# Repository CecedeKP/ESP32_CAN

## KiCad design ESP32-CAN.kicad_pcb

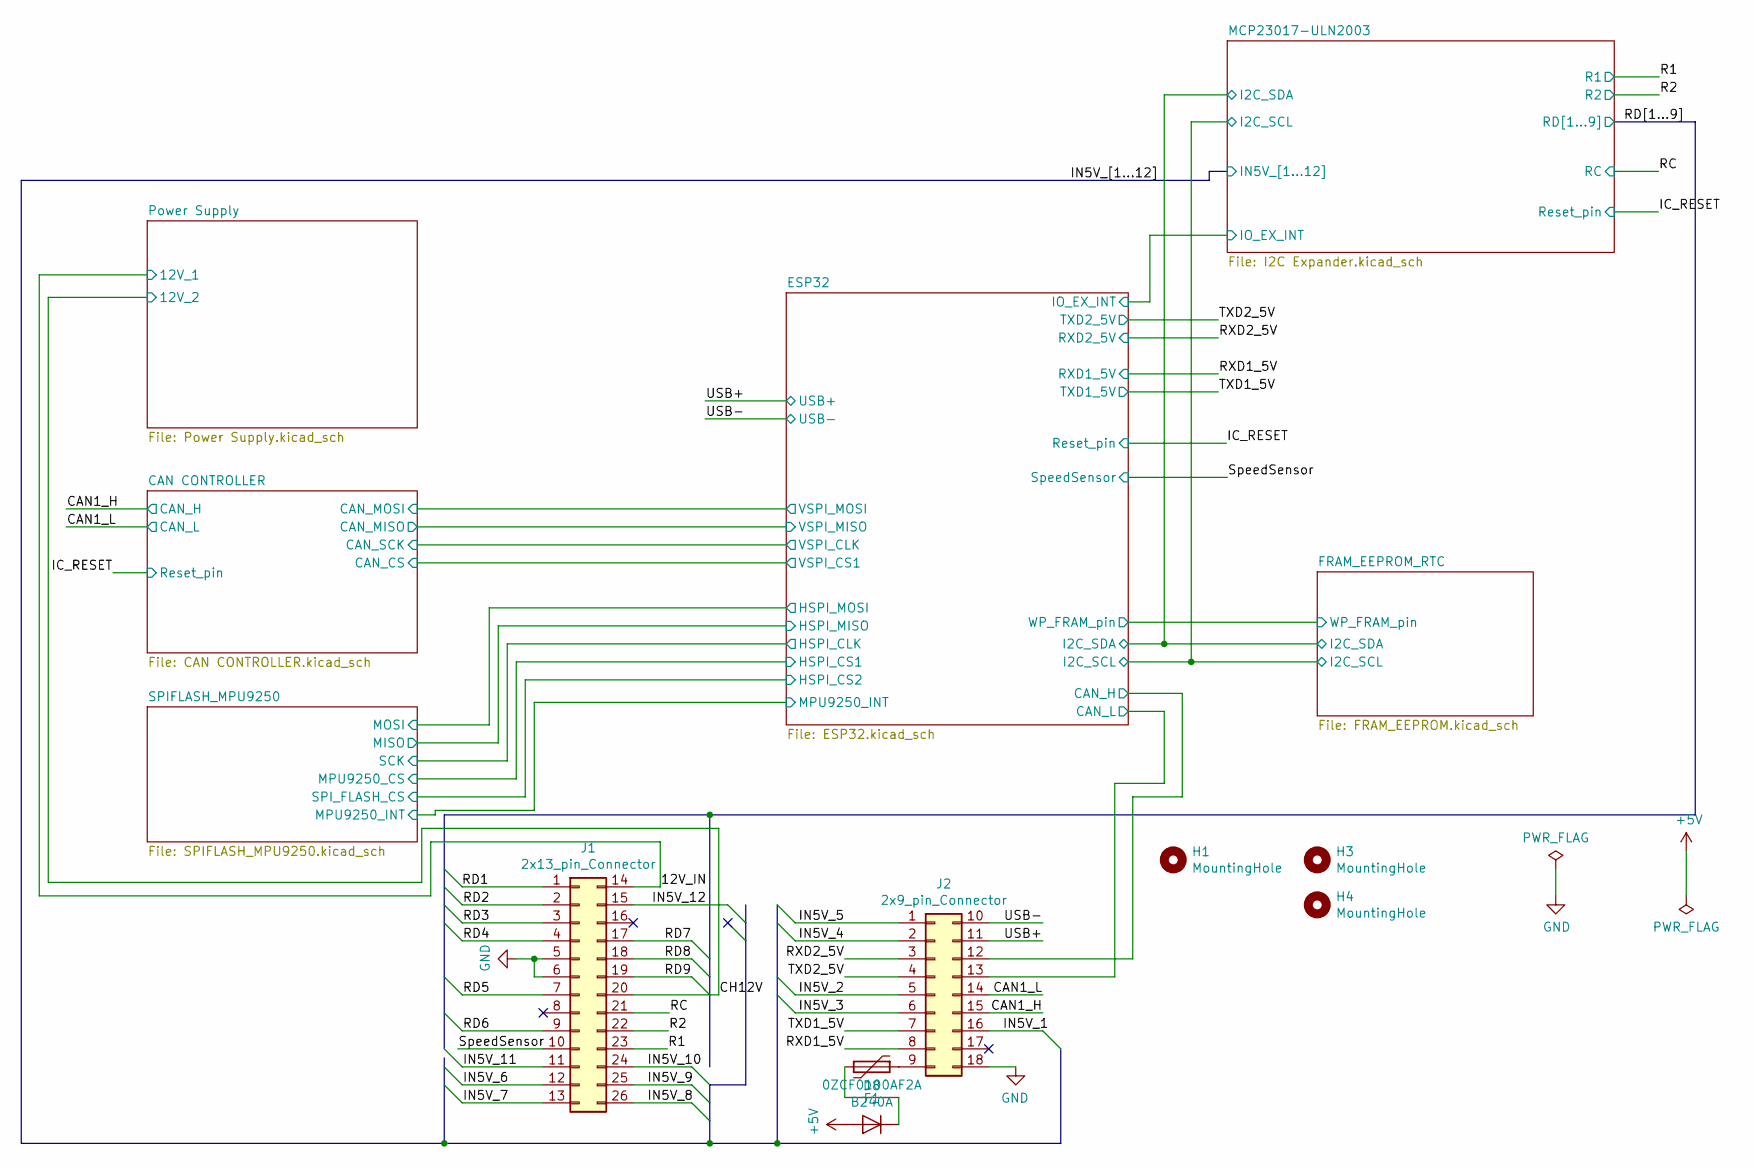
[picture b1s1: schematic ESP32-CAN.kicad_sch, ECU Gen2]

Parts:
D8: B240A; D_SMA
F1: 0ZCF0100AF2A; Fuse_2920_7451Metric
H1, H3, H4: MountingHole; MountingHole_3.2mm_M3_Pad_Via
J1: 2x13_pin_Connector; 3126A0312
J2: 2x9_pin_Connector; 3118A0312

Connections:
+5V: D8.2 (A); also elsewhere on the board
/12V_IN: J1.14; also elsewhere on the board
/CAN1_H: J2.15; also elsewhere on the board
/CAN1_L: J2.14; also elsewhere on the board
/CH12V: J1.20; also elsewhere on the board
/ESP32/CAN_H: J2.12; also elsewhere on the board
/ESP32/CAN_L: J2.13; also elsewhere on the board
/IN5V_1: J2.16; also elsewhere on the board
/IN5V_2: J2.5; also elsewhere on the board
/IN5V_3: J2.6; also elsewhere on the board
/IN5V_4: J2.2; also elsewhere on the board
/IN5V_5: J2.1; also elsewhere on the board
/IN5V_6: J1.12; also elsewhere on the board
/IN5V_7: J1.13; also elsewhere on the board
/IN5V_8: J1.26; also elsewhere on the board
/IN5V_9: J1.25; also elsewhere on the board
/IN5V_10: J1.24; also elsewhere on the board
/IN5V_11: J1.11; also elsewhere on the board
/IN5V_12: J1.15; also elsewhere on the board
/R1: J1.23; also elsewhere on the board
/R2: J1.22; also elsewhere on the board
/RC: J1.21; also elsewhere on the board
/RD1: J1.1; also elsewhere on the board
/RD2: J1.2; also elsewhere on the board
/RD3: J1.3; also elsewhere on the board
/RD4: J1.4; also elsewhere on the board
/RD5: J1.7; also elsewhere on the board
/RD6: J1.9; also elsewhere on the board
/RD7: J1.17; also elsewhere on the board
/RD8: J1.18; also elsewhere on the board
/RD9: J1.19; also elsewhere on the board
/RXD1_5V: J2.8; also elsewhere on the board
/RXD2_5V: J2.3; also elsewhere on the board
/SpeedSensor: J1.10; also elsewhere on the board
/TXD1_5V: J2.7; also elsewhere on the board
/TXD2_5V: J2.4; also elsewhere on the board
/USB+: J2.11; also elsewhere on the board
/USB-: J2.10; also elsewhere on the board
GND: J1.5, J1.6, J2.18; also elsewhere on the board
unnamed: D8.1 (K), F1.2
unnamed: F1.1, J2.9

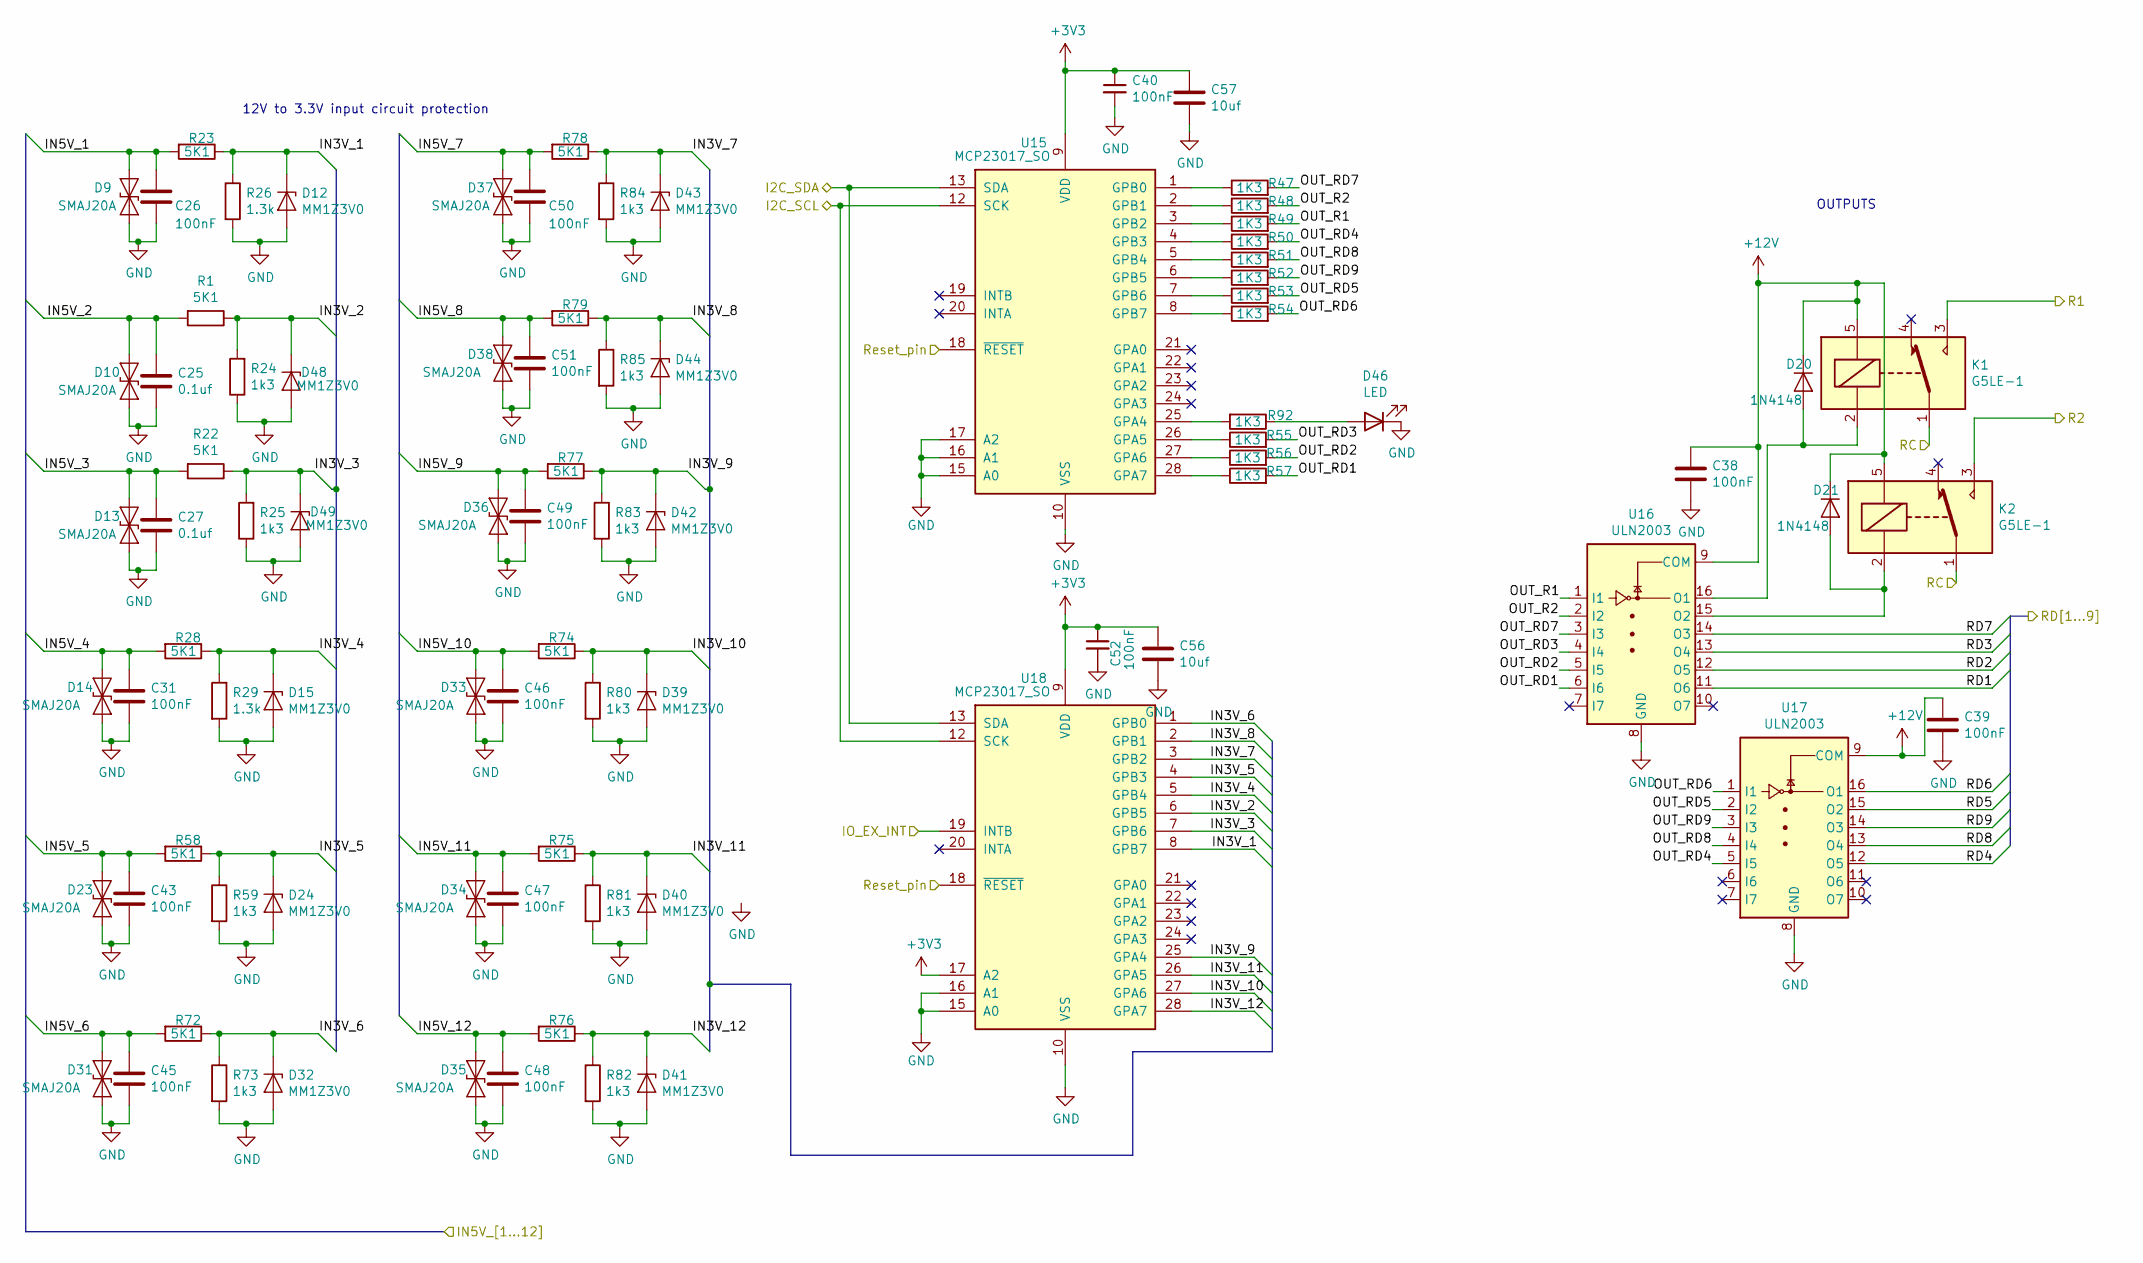
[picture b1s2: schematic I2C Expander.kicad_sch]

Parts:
C25, C27: 0.1uf; C_0603_1608Metric
C26, C31, C38, C39, C40, C43, C45, C46, C47, C48, C49, C50, C51, C52: 100nF; C_0603_1608Metric
C56, C57: 10uf; C_0603_1608Metric
D9, D10, D13, D14, D23, D31, D33, D34, D35, D36, D37, D38: SMAJ20A; D_SMA
D12, D15, D24, D32, D39, D40, D41, D42, D43, D44, D48, D49: MM1Z3V0; D_SOD-123
D20, D21: 1N4148; D_MiniMELF
D46: LED; LED_0603_1608Metric
K1, K2: G5LE-1; Relay_SPDT_Omron-G5LE-1
R1, R22, R23, R28, R58, R72, R74, R75, R76, R77, R78, R79: 5K1; R_0603_1608Metric
R24, R25, R59, R73, R80, R81, R82, R83, R84, R85: 1k3; R_0603_1608Metric
R26, R29: 1.3k; R_0603_1608Metric
R47, R48, R49, R50, R51, R52, R53, R54, R55, R56, R57, R92: 1K3; R_0603_1608Metric
U15, U18: MCP23017_SO; SOIC-28W_7.5x17.9mm_P1.27mm
U16, U17: ULN2003; SOIC-16_3.9x9.9mm_P1.27mm

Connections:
+12V: C38.1, C39.1, D20.1 (K), D21.1 (K), K1.5, K2.5, U16.9 (COM), U17.9 (COM); also elsewhere on the board
/ESP32/I2C_SCL: U15.12 (SCK), U18.12 (SCK); also elsewhere on the board
/ESP32/I2C_SDA: U15.13 (SDA), U18.13 (SDA); also elsewhere on the board
/ESP32/IO_EX_INT: U18.19 (INTB); also elsewhere on the board
/IC_RESET: U15.18 (~RESET), U18.18 (~RESET); also elsewhere on the board
/IN5V_1: C26.1, D9.1 (A1), R23.2; also elsewhere on the board
/IN5V_2: C25.1, D10.1 (A1), R1.2; also elsewhere on the board
/IN5V_3: C27.1, D13.1 (A1), R22.2; also elsewhere on the board
/IN5V_4: C31.1, D14.1 (A1), R28.2; also elsewhere on the board
/IN5V_5: C43.1, D23.1 (A1), R58.2; also elsewhere on the board
/IN5V_6: C45.1, D31.1 (A1), R72.2; also elsewhere on the board
/IN5V_7: C50.1, D37.1 (A1), R78.2; also elsewhere on the board
/IN5V_8: C51.1, D38.1 (A1), R79.2; also elsewhere on the board
/IN5V_9: C49.1, D36.1 (A1), R77.2; also elsewhere on the board
/IN5V_10: C46.1, D33.1 (A1), R74.2; also elsewhere on the board
/IN5V_11: C47.1, D34.1 (A1), R75.2; also elsewhere on the board
/IN5V_12: C48.1, D35.1 (A1), R76.2; also elsewhere on the board
/MCP23017-ULN2003/IN3V_1: D12.1 (K), R23.1, R26.1, U18.8 (GPB7)
/MCP23017-ULN2003/IN3V_2: D48.1 (K), R1.1, R24.2, U18.6 (GPB5)
/MCP23017-ULN2003/IN3V_3: D49.1 (K), R22.1, R25.2, U18.7 (GPB6)
/MCP23017-ULN2003/IN3V_4: D15.1 (K), R28.1, R29.1, U18.5 (GPB4)
/MCP23017-ULN2003/IN3V_5: D24.1 (K), R58.1, R59.1, U18.4 (GPB3)
/MCP23017-ULN2003/IN3V_6: D32.1 (K), R72.1, R73.1, U18.1 (GPB0)
/MCP23017-ULN2003/IN3V_7: D43.1 (K), R78.1, R84.1, U18.3 (GPB2)
/MCP23017-ULN2003/IN3V_8: D44.1 (K), R79.1, R85.1, U18.2 (GPB1)
/MCP23017-ULN2003/IN3V_9: D42.1 (K), R77.1, R83.1, U18.25 (GPA4)
/MCP23017-ULN2003/IN3V_10: D39.1 (K), R74.1, R80.1, U18.27 (GPA6)
/MCP23017-ULN2003/IN3V_11: D40.1 (K), R75.1, R81.1, U18.26 (GPA5)
/MCP23017-ULN2003/IN3V_12: D41.1 (K), R76.1, R82.1, U18.28 (GPA7)
/MCP23017-ULN2003/OUT_R1: R49.2, U16.1 (I1)
/MCP23017-ULN2003/OUT_R2: R48.2, U16.2 (I2)
/MCP23017-ULN2003/OUT_RD1: R57.2, U16.6 (I6)
/MCP23017-ULN2003/OUT_RD2: R56.2, U16.5 (I5)
/MCP23017-ULN2003/OUT_RD3: R55.2, U16.4 (I4)
/MCP23017-ULN2003/OUT_RD4: R50.2, U17.5 (I5)
/MCP23017-ULN2003/OUT_RD5: R53.2, U17.2 (I2)
/MCP23017-ULN2003/OUT_RD6: R54.2, U17.1 (I1)
/MCP23017-ULN2003/OUT_RD7: R47.2, U16.3 (I3)
/MCP23017-ULN2003/OUT_RD8: R51.2, U17.4 (I4)
/MCP23017-ULN2003/OUT_RD9: R52.2, U17.3 (I3)
/R1: K1.3; also elsewhere on the board
/R2: K2.3; also elsewhere on the board
/RC: K1.1, K2.1; also elsewhere on the board
/RD1: U16.11 (O6); also elsewhere on the board
/RD2: U16.12 (O5); also elsewhere on the board
/RD3: U16.13 (O4); also elsewhere on the board
/RD4: U17.12 (O5); also elsewhere on the board
/RD5: U17.15 (O2); also elsewhere on the board
/RD6: U17.16 (O1); also elsewhere on the board
/RD7: U16.14 (O3); also elsewhere on the board
/RD8: U17.13 (O4); also elsewhere on the board
/RD9: U17.14 (O3); also elsewhere on the board
GND: C25.2, C26.2, C27.2, C31.2, C38.2, C39.2, C40.2, C43.2, C45.2, C46.2, C47.2, C48.2, C49.2, C50.2, C51.2, C52.2, C56.2, C57.2, D9.2 (A2), D10.2 (A2), D12.2 (A), D13.2 (A2), D14.2 (A2), D15.2 (A), D23.2 (A2), D24.2 (A), D31.2 (A2), D32.2 (A), D33.2 (A2), D34.2 (A2), D35.2 (A2), D36.2 (A2), D37.2 (A2), D38.2 (A2), D39.2 (A), D40.2 (A), D41.2 (A), D42.2 (A), D43.2 (A), D44.2 (A), D46.1 (K), D48.2 (A), D49.2 (A), R24.1, R25.1, R26.2, R29.2, R59.2, R73.2, R80.2, R81.2, R82.2, R83.2, R84.2, R85.2, U15.10 (VSS), U15.15 (A0), U15.16 (A1), U15.17 (A2), U16.8 (GND), U17.8 (GND), U18.10 (VSS), U18.15 (A0), U18.16 (A1); also elsewhere on the board
unnamed: D20.2 (A), K1.2, U16.16 (O1)
unnamed: D21.2 (A), K2.2, U16.15 (O2)
unnamed: D46.2 (A), R92.1
unnamed: R47.1, U15.1 (GPB0)
unnamed: R48.1, U15.2 (GPB1)
unnamed: R49.1, U15.3 (GPB2)
unnamed: R50.1, U15.4 (GPB3)
unnamed: R51.1, U15.5 (GPB4)
unnamed: R52.1, U15.6 (GPB5)
unnamed: R53.1, U15.7 (GPB6)
unnamed: R54.1, U15.8 (GPB7)
unnamed: R55.1, U15.26 (GPA5)
unnamed: R56.1, U15.27 (GPA6)
unnamed: R57.1, U15.28 (GPA7)
unnamed: R92.2, U15.25 (GPA4)

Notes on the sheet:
OUTPUTS
12V to 3.3V input circuit protection

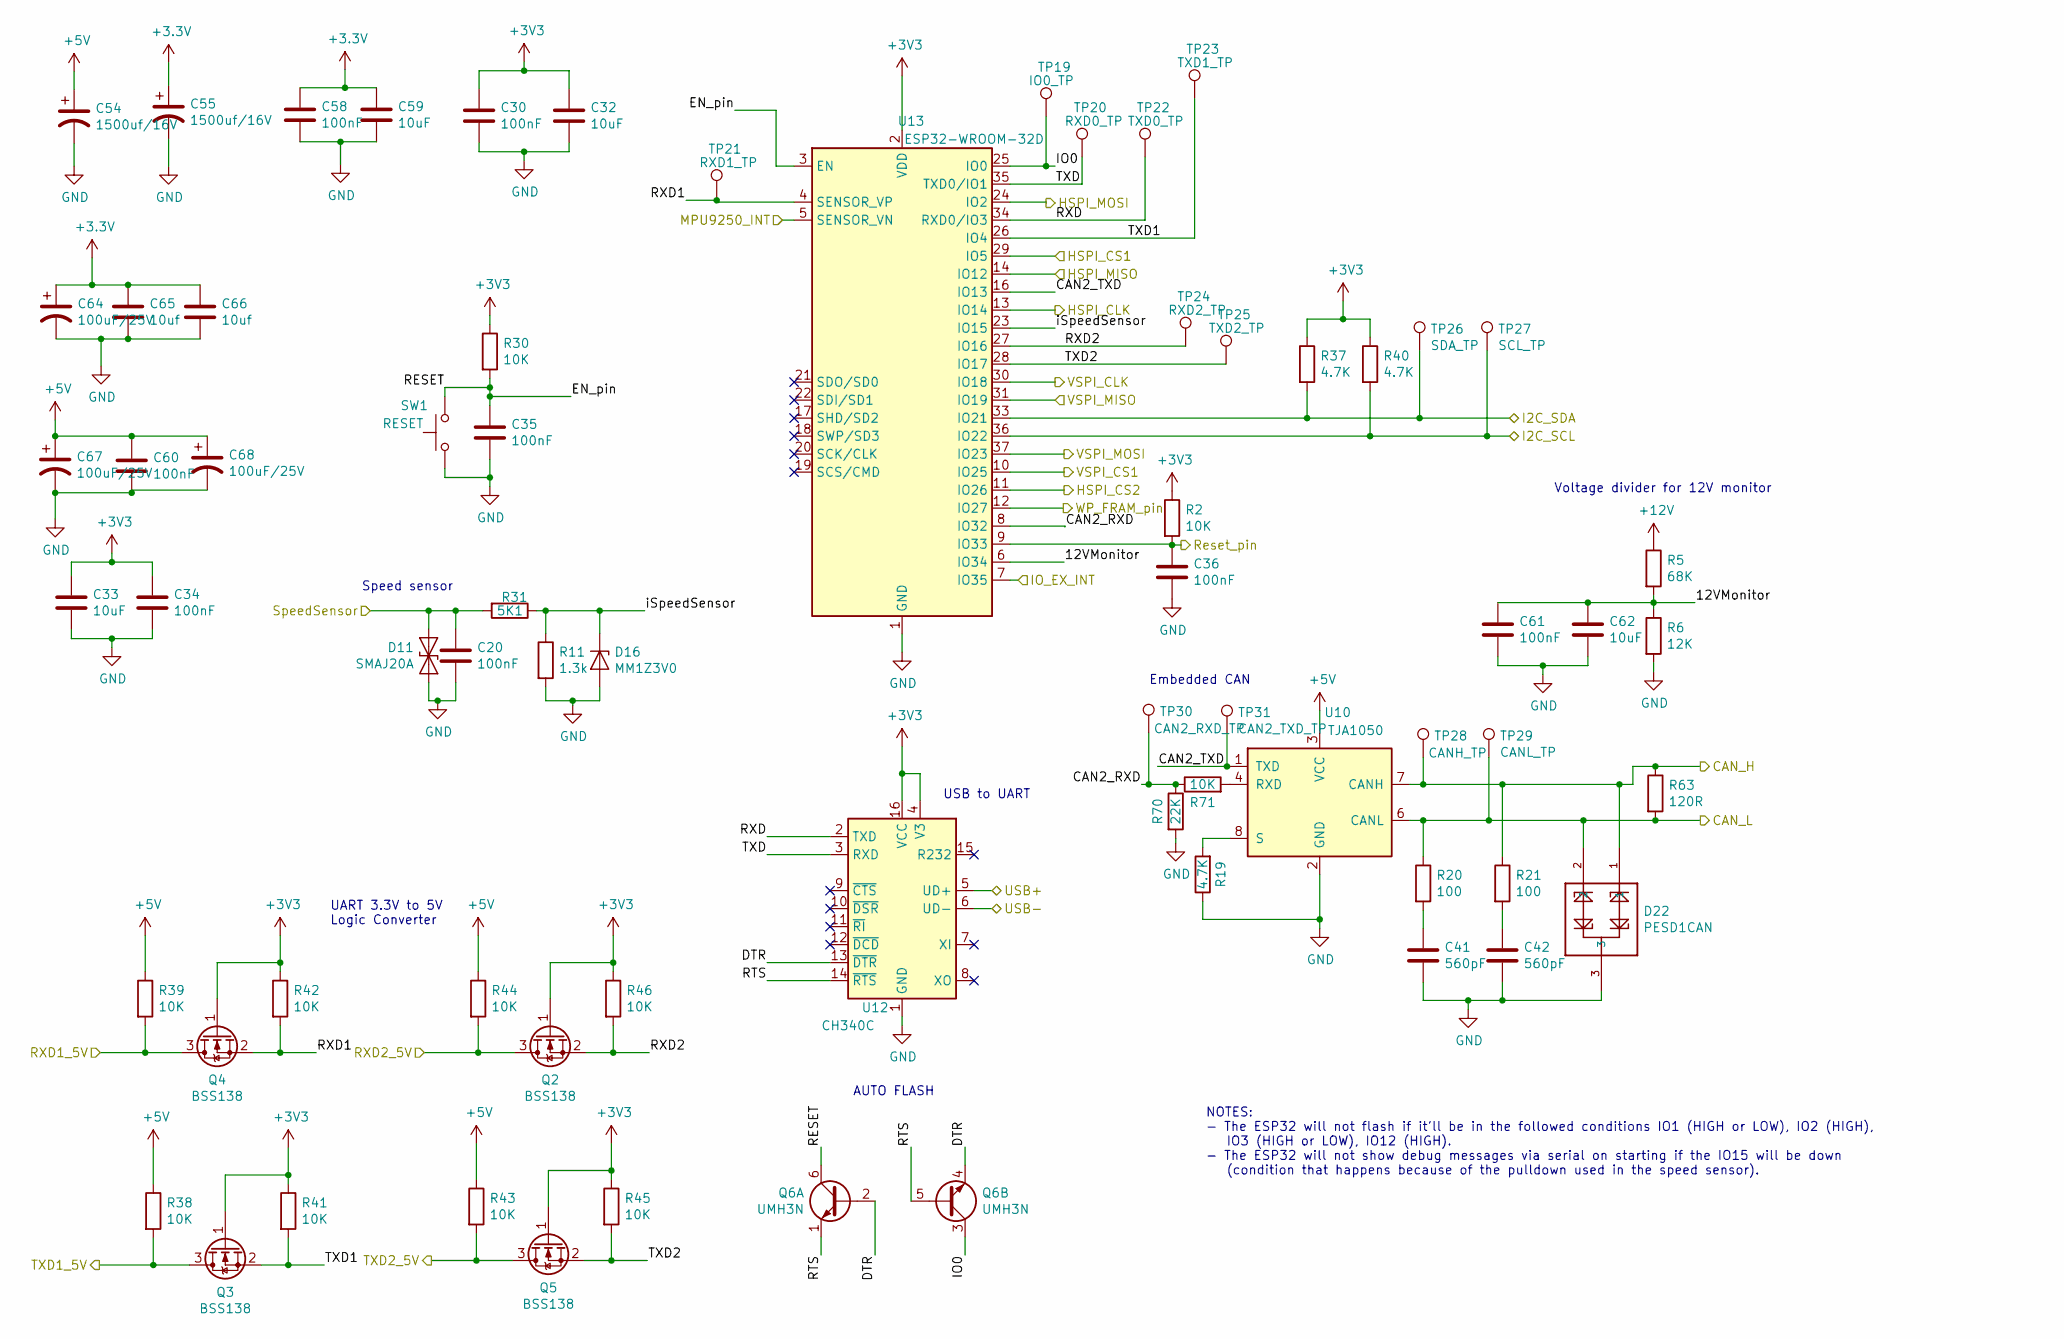
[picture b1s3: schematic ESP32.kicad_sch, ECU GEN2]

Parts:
C20, C30, C34, C35, C36, C58, C60, C61: 100nF; C_0603_1608Metric
C32, C33, C59, C62: 10uF; C_0603_1608Metric
C41, C42: 560pF; C_0603_1608Metric
C54, C55: 1500uf/16V; CP_Radial_D10.0mm_P5.00mm
C64, C67, C68: 100uF/25V; CP_Elec_6.3x5.8
C65, C66: 10uf; C_1206_3216Metric
D11: SMAJ20A; D_SMA
D16: MM1Z3V0; D_SOD-123
D22: PESD1CAN; SOT-23
Q2, Q3, Q4, Q5: BSS138; SOT-23
Q6: UMH3N; SOT-363_SC-70-6
R2, R30, R38, R39, R41, R42, R43, R44, R45, R46, R71: 10K; R_0603_1608Metric
R5: 68K; R_0603_1608Metric; Tolerance 1%
R6: 12K; R_0603_1608Metric; Tolerance 1%
R11: 1.3k; R_0603_1608Metric
R19, R37, R40: 4.7K; R_0603_1608Metric
R20, R21: 100; R_0603_1608Metric
R31: 5K1; R_0603_1608Metric
R63: 120R; R_1206_3216Metric
R70: 22K; R_0603_1608Metric
SW1: RESET; SW_SPST_PTS645
TP19: IO0_TP; TestPoint_Pad_D1.0mm
TP20: RXD0_TP; TestPoint_Pad_D1.0mm
TP21: RXD1_TP; TestPoint_Pad_D1.0mm
TP22: TXD0_TP; TestPoint_Pad_D1.0mm
TP23: TXD1_TP; TestPoint_Pad_D1.0mm
TP24: RXD2_TP; TestPoint_Pad_D1.0mm
TP25: TXD2_TP; TestPoint_Pad_D1.0mm
TP26: SDA_TP; TestPoint_Pad_D1.0mm
TP27: SCL_TP; TestPoint_Pad_D1.0mm
TP28: CANH_TP; TestPoint_Pad_D1.0mm
TP29: CANL_TP; TestPoint_Pad_D1.0mm
TP30: CAN2_RXD_TP; TestPoint_Pad_D1.0mm
TP31: CAN2_TXD_TP; TestPoint_Pad_D1.0mm
U10: TJA1050; SOIC-8_3.9x4.9mm_P1.27mm
U12: CH340C; SOIC-16_3.9x9.9mm_P1.27mm
U13: ESP32-WROOM-32D; ESP32-WROOM-32

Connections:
+5V: C54.1, C60.1, C67.1, C68.1, R38.1, R39.1, R43.1, R44.1, U10.3 (VCC); also elsewhere on the board
+12V: R5.1; also elsewhere on the board
/CAN CONTROLLER/CAN_CS: U13.10 (IO25); also elsewhere on the board
/CAN CONTROLLER/CAN_MISO: U13.31 (IO19); also elsewhere on the board
/CAN CONTROLLER/CAN_MOSI: U13.37 (IO23); also elsewhere on the board
/CAN CONTROLLER/CAN_SCK: U13.30 (IO18); also elsewhere on the board
/ESP32/12VMonitor: C61.1, C62.1, R5.2, R6.1, U13.6 (IO34)
/ESP32/CAN2_RXD: R70.1, R71.1, TP30.1, U13.8 (IO32)
/ESP32/CAN2_TXD: TP31.1, U10.1 (TXD), U13.16 (IO13)
/ESP32/CAN_H: D22.1, R21.1, R63.1, TP28.1, U10.7 (CANH); also elsewhere on the board
/ESP32/CAN_L: D22.2, R20.1, R63.2, TP29.1, U10.6 (CANL); also elsewhere on the board
/ESP32/DTR: Q6.2 (B1), Q6.4 (E2), U12.13 (~DTR)
/ESP32/EN_pin: C35.1, Q6.6 (C1), R30.2, SW1.2, U13.3 (EN)
/ESP32/HSPI_CLK: U13.13 (IO14); also elsewhere on the board
/ESP32/HSPI_CS1: U13.29 (IO5); also elsewhere on the board
/ESP32/HSPI_CS2: U13.11 (IO26); also elsewhere on the board
/ESP32/HSPI_MISO: U13.14 (IO12); also elsewhere on the board
/ESP32/HSPI_MOSI: U13.24 (IO2); also elsewhere on the board
/ESP32/I2C_SCL: R40.2, TP27.1, U13.36 (IO22); also elsewhere on the board
/ESP32/I2C_SDA: R37.2, TP26.1, U13.33 (IO21); also elsewhere on the board
/ESP32/IO0: Q6.3 (C2), TP19.1, U13.25 (IO0)
/ESP32/IO_EX_INT: U13.7 (IO35); also elsewhere on the board
/ESP32/MPU9250_INT: U13.5 (SENSOR_VN); also elsewhere on the board
/ESP32/RTS: Q6.1 (E1), Q6.5 (B2), U12.14 (~RTS)
/ESP32/RXD: TP22.1, U12.2 (TXD), U13.34 (RXD0/IO3)
/ESP32/RXD1: Q4.2 (S), R42.2, TP21.1, U13.4 (SENSOR_VP)
/ESP32/RXD2: Q2.2 (S), R46.2, TP24.1, U13.27 (IO16)
/ESP32/TXD: TP20.1, U12.3 (RXD), U13.35 (TXD0/IO1)
/ESP32/TXD1: Q3.2 (S), R41.2, TP23.1, U13.26 (IO4)
/ESP32/TXD2: Q5.2 (S), R45.2, TP25.1, U13.28 (IO17)
/ESP32/WP_FRAM_pin: U13.12 (IO27); also elsewhere on the board
/ESP32/iSpeedSensor: D16.1 (K), R11.1, R31.1, U13.23 (IO15)
/IC_RESET: C36.1, R2.2, U13.9 (IO33); also elsewhere on the board
/RXD1_5V: Q4.3 (D), R39.2; also elsewhere on the board
/RXD2_5V: Q2.3 (D), R44.2; also elsewhere on the board
/SpeedSensor: C20.1, D11.1 (A1), R31.2; also elsewhere on the board
/TXD1_5V: Q3.3 (D), R38.2; also elsewhere on the board
/TXD2_5V: Q5.3 (D), R43.2; also elsewhere on the board
/USB+: U12.5 (UD+); also elsewhere on the board
/USB-: U12.6 (UD-); also elsewhere on the board
GND: C20.2, C30.2, C32.2, C33.2, C34.2, C35.2, C36.2, C41.2, C42.2, C54.2, C55.2, C58.2, C59.2, C60.2, C61.2, C62.2, C64.2, C65.2, C66.2, C67.2, C68.2, D11.2 (A2), D16.2 (A), D22.3, R6.2, R11.2, R19.1, R70.2, SW1.1, U10.2 (GND), U12.1 (GND), U13.1 (GND), U13.15 (GND), U13.38 (GND); also elsewhere on the board
unnamed: C41.1, R20.2
unnamed: C42.1, R21.2
unnamed: R19.2, U10.8 (S)
unnamed: R71.2, U10.4 (RXD)

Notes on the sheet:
UART 3.3V to 5V Logic Converter
USB to UART
Voltage divider for 12V monitor
Speed sensor
NOTES: - The ESP32 will not flash if it'll be in the followed conditions IO1 (HIGH or LOW), IO2 (HIGH), IO3 (HIGH or LOW), IO12 (HIGH). - The ESP32 will not show debug messages via serial on starting if the IO15 will be down (condition that happens because of the pulldown used in the speed sensor).
Embedded CAN
AUTO FLASH

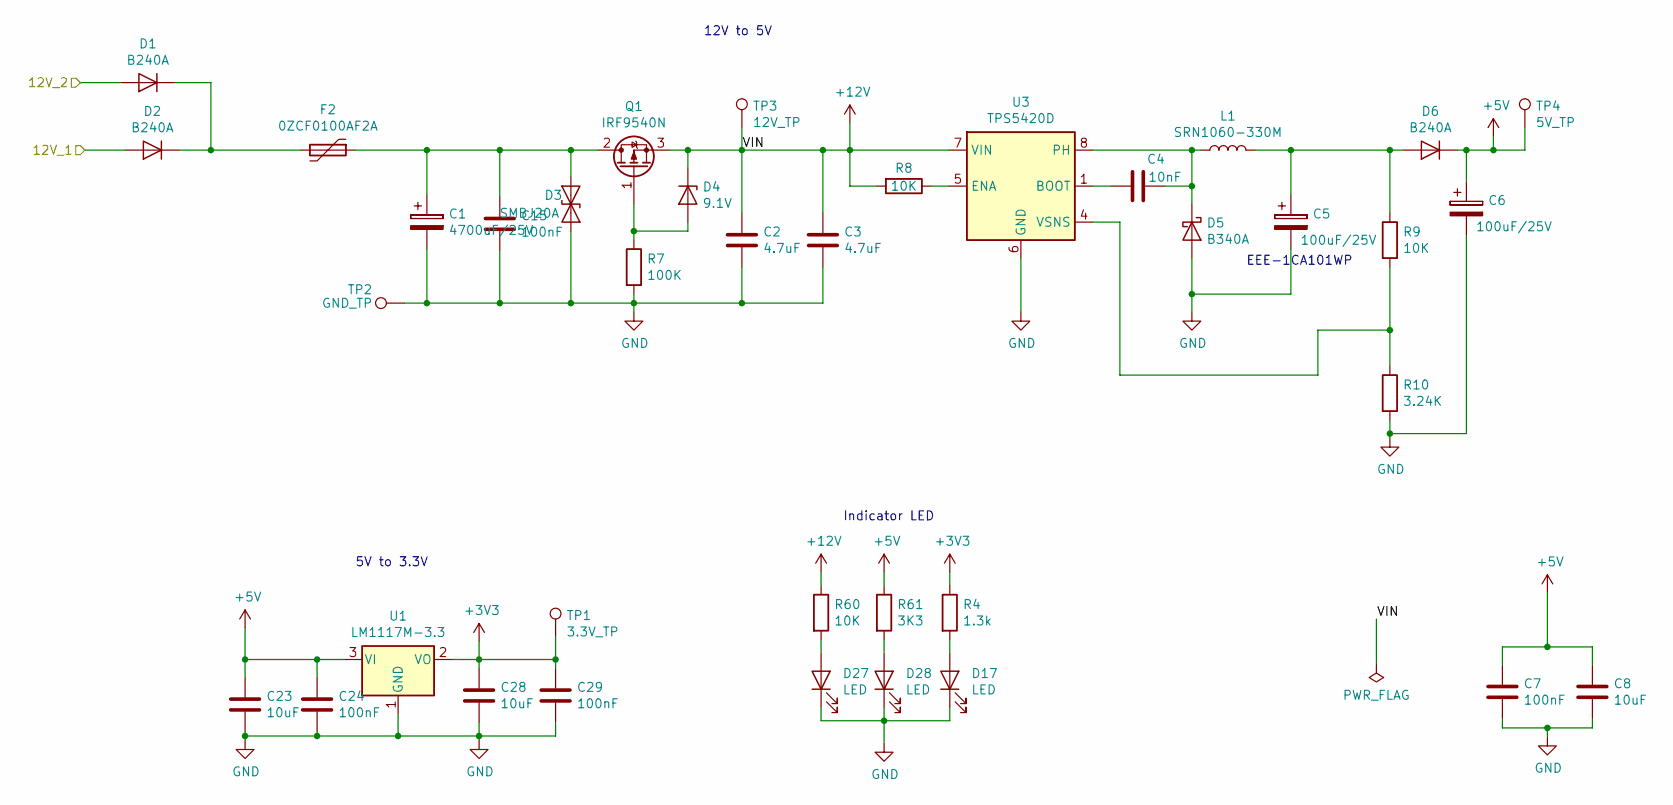
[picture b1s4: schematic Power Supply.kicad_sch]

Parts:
C1: 4700uF/25V; CP_Radial_D16.0mm_P7.50mm
C2, C3: 4.7uF; C_1206_3216Metric
C4: 10nF; C_0603_1608Metric
C5, C6: 100uF/25V; CP_Elec_6.3x5.8
C7, C15, C24, C29: 100nF; C_0603_1608Metric
C8, C23, C28: 10uF; C_0603_1608Metric
D1, D2, D6: B240A; D_SMA
D3: SMBJ20A; D_SMB
D4: 9.1V; D_SOD-123
D5: B340A; D_SMA
D17, D27, D28: LED; LED_0603_1608Metric
F2: 0ZCF0100AF2A; Fuse_2920_7451Metric
L1: SRN1060-330M; L_Bourns-SRN1060
Q1: IRF9540N; TO-220-3_Horizontal_TabDown
R4: 1.3k; R_0603_1608Metric
R7: 100K; R_0603_1608Metric
R8, R9, R60: 10K; R_0603_1608Metric
R10: 3.24K; R_0603_1608Metric
R61: 3K3; R_0603_1608Metric
TP1: 3.3V_TP; TestPoint_Pad_D1.0mm
TP2: GND_TP; TestPoint_Pad_D1.0mm
TP3: 12V_TP; TestPoint_Pad_D1.0mm
TP4: 5V_TP; TestPoint_Pad_D1.0mm
U1: LM1117M-3.3; SOT-223-3_TabPin2
U3: TPS5420D; SOIC-8_3.9x4.9mm_P1.27mm

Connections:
+5V: C6.1, C7.1, C8.1, C23.1, C24.1, D6.1 (K), R61.1, TP4.1, U1.3 (VI); also elsewhere on the board
+12V: C2.1, C3.1, D4.1 (K), Q1.3 (S), R8.2, R60.1, TP3.1, U3.7 (VIN); also elsewhere on the board
/12V_IN: D2.2 (A); also elsewhere on the board
/CH12V: D1.2 (A); also elsewhere on the board
GND: C1.2, C2.2, C3.2, C5.2, C6.2, C7.2, C8.2, C15.2, C23.2, C24.2, C28.2, C29.2, D3.2 (A2), D5.2 (A), D17.1 (K), D27.1 (K), D28.1 (K), R7.2, R10.2, TP2.1, U1.1 (GND), U3.6 (GND); also elsewhere on the board
unnamed: C1.1, C15.1, D3.1 (A1), F2.1, Q1.2 (D)
unnamed: C4.1, D5.1 (K), L1.1, U3.8 (PH)
unnamed: C4.2, U3.1 (BOOT)
unnamed: C5.1, D6.2 (A), L1.2, R9.1
unnamed: D1.1 (K), D2.1 (K), F2.2
unnamed: D4.2 (A), Q1.1 (G), R7.1
unnamed: D17.2 (A), R4.2
unnamed: D27.2 (A), R60.2
unnamed: D28.2 (A), R61.2
unnamed: R8.1, U3.5 (ENA)
unnamed: R9.2, R10.1, U3.4 (VSNS)

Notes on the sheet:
12V to 5V
EEE-1CA101WP
Indicator LED
5V to 3.3V

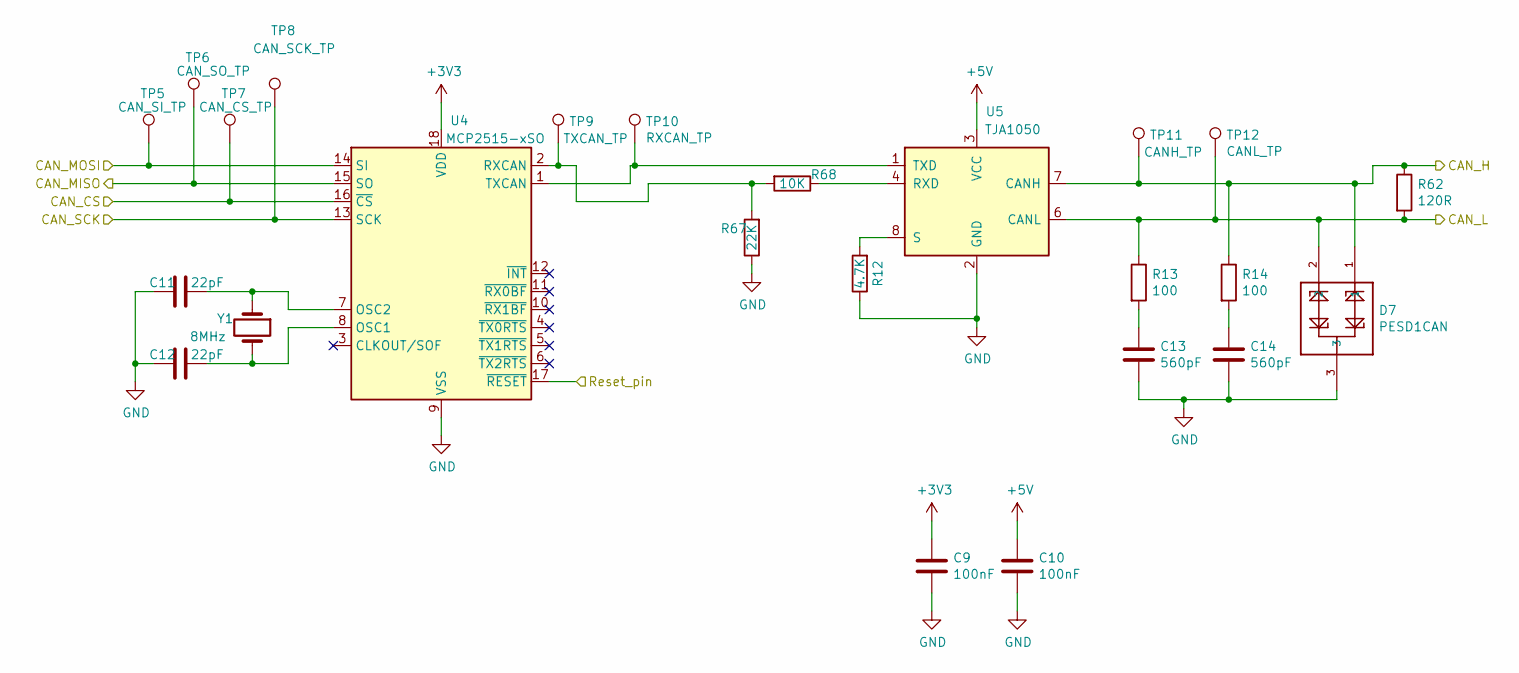
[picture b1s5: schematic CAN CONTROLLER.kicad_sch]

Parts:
C9, C10: 100nF; C_0603_1608Metric
C11, C12: 22pF; C_0603_1608Metric
C13, C14: 560pF; C_0603_1608Metric
D7: PESD1CAN; SOT-23
R12: 4.7K; R_0603_1608Metric
R13, R14: 100; R_0603_1608Metric
R62: 120R; R_1206_3216Metric
R67: 22K; R_0603_1608Metric
R68: 10K; R_0603_1608Metric
TP5: CAN_SI_TP; TestPoint_Pad_D1.0mm
TP6: CAN_SO_TP; TestPoint_Pad_D1.0mm
TP7: CAN_CS_TP; TestPoint_Pad_D1.0mm
TP8: CAN_SCK_TP; TestPoint_Pad_D1.0mm
TP9: TXCAN_TP; TestPoint_Pad_D1.0mm
TP10: RXCAN_TP; TestPoint_Pad_D1.0mm
TP11: CANH_TP; TestPoint_Pad_D1.0mm
TP12: CANL_TP; TestPoint_Pad_D1.0mm
U4: MCP2515-xSO; SOIC-18W_7.5x11.6mm_P1.27mm
U5: TJA1050; SOIC-8_3.9x4.9mm_P1.27mm
Y1: 8MHz; Crystal_SMD_5032-2Pin_5.0x3.2mm

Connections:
+5V: C10.1, U5.3 (VCC); also elsewhere on the board
/CAN1_H: D7.1, R14.1, R62.1, TP11.1, U5.7 (CANH); also elsewhere on the board
/CAN1_L: D7.2, R13.1, R62.2, TP12.1, U5.6 (CANL); also elsewhere on the board
/CAN CONTROLLER/CAN_CS: TP7.1, U4.16 (~CS); also elsewhere on the board
/CAN CONTROLLER/CAN_MISO: TP6.1, U4.15 (SO); also elsewhere on the board
/CAN CONTROLLER/CAN_MOSI: TP5.1, U4.14 (SI); also elsewhere on the board
/CAN CONTROLLER/CAN_SCK: TP8.1, U4.13 (SCK); also elsewhere on the board
/IC_RESET: U4.17 (~RESET); also elsewhere on the board
GND: C9.2, C10.2, C11.2, C12.2, C13.2, C14.2, D7.3, R12.1, R67.1, U4.9 (VSS), U5.2 (GND); also elsewhere on the board
unnamed: C11.1, U4.7 (OSC2), Y1.1
unnamed: C12.1, U4.8 (OSC1), Y1.2
unnamed: C13.1, R13.2
unnamed: C14.1, R14.2
unnamed: R12.2, U5.8 (S)
unnamed: R67.2, R68.2, TP9.1, U4.2 (RXCAN)
unnamed: R68.1, U5.4 (RXD)
unnamed: TP10.1, U4.1 (TXCAN), U5.1 (TXD)

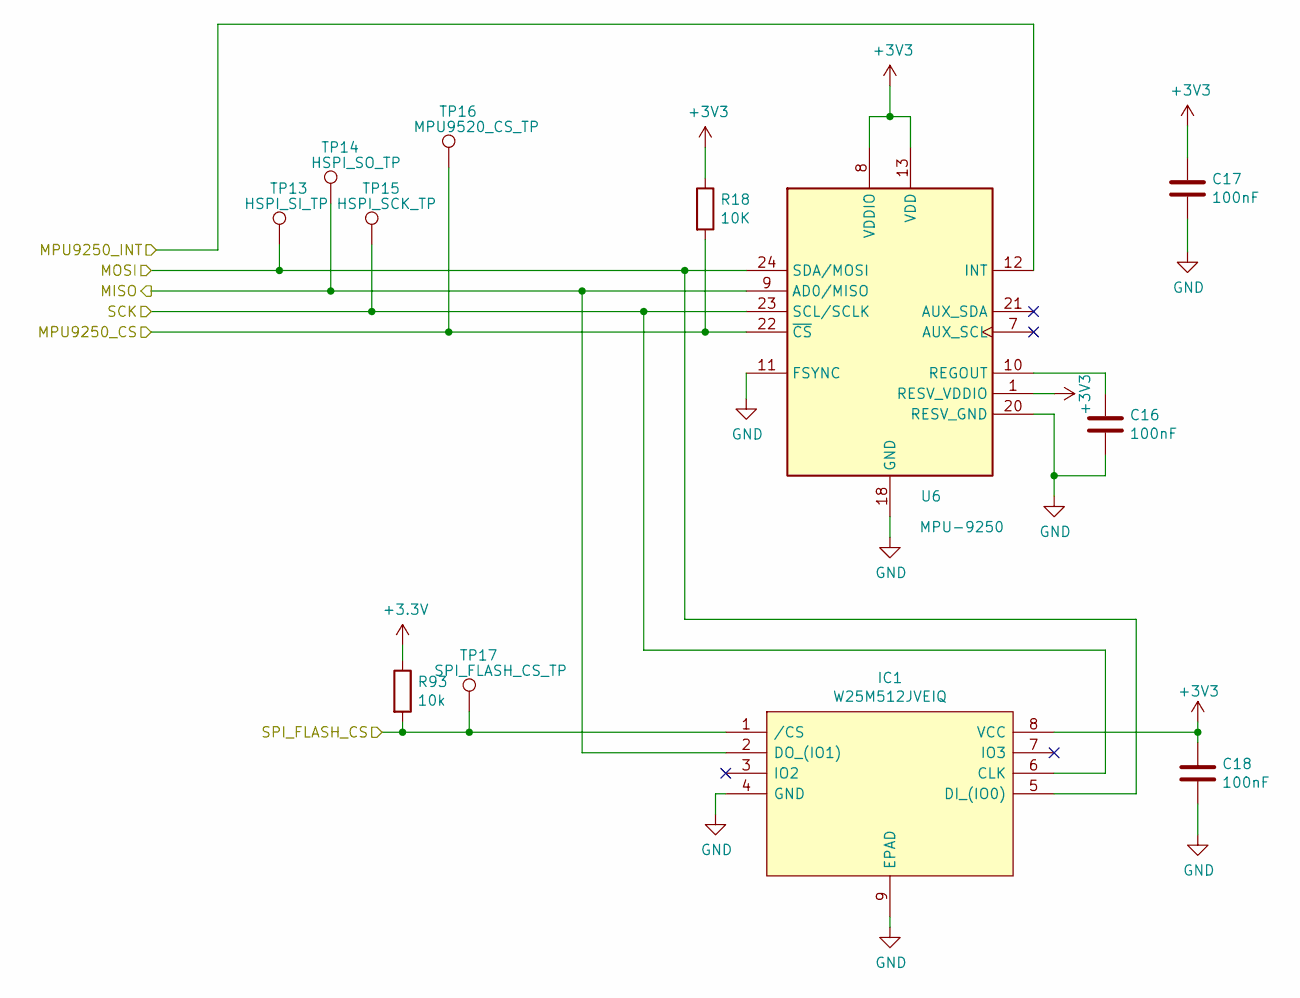
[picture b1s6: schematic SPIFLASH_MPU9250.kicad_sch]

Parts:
C16, C17, C18: 100nF; C_0603_1608Metric
IC1: W25M512JVEIQ; SON127P800X600X80-9N-D; Manufacturer_Part_Number W25M512JVEIQ; Mouser Part Number 454-W25M512JVEIQ
R18: 10K; R_0603_1608Metric
R93: 10k; R_0603_1608Metric
TP13: HSPI_SI_TP; TestPoint_Pad_D1.0mm
TP14: HSPI_SO_TP; TestPoint_Pad_D1.0mm
TP15: HSPI_SCK_TP; TestPoint_Pad_D1.0mm
TP16: MPU9520_CS_TP; TestPoint_Pad_D1.0mm
TP17: SPI_FLASH_CS_TP; TestPoint_Pad_D1.0mm
U6: MPU-9250; QFN-24-1EP_3x3mm_P0.4mm_EP1.75x1.6mm

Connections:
/ESP32/HSPI_CLK: IC1.6 (CLK), TP15.1, U6.23 (SCL/SCLK); also elsewhere on the board
/ESP32/HSPI_CS1: R18.2, TP16.1, U6.22 (~CS); also elsewhere on the board
/ESP32/HSPI_CS2: IC1.1 (/CS), R93.2, TP17.1; also elsewhere on the board
/ESP32/HSPI_MISO: IC1.2 (DO_(IO1)), TP14.1, U6.9 (AD0/MISO); also elsewhere on the board
/ESP32/HSPI_MOSI: IC1.5 (DI_(IO0)), TP13.1, U6.24 (SDA/MOSI); also elsewhere on the board
/ESP32/MPU9250_INT: U6.12 (INT); also elsewhere on the board
GND: C16.2, C17.2, C18.2, IC1.4 (GND), IC1.9 (EPAD), U6.11 (FSYNC), U6.18 (GND), U6.20 (RESV_GND); also elsewhere on the board
unnamed: C16.1, U6.10 (REGOUT)

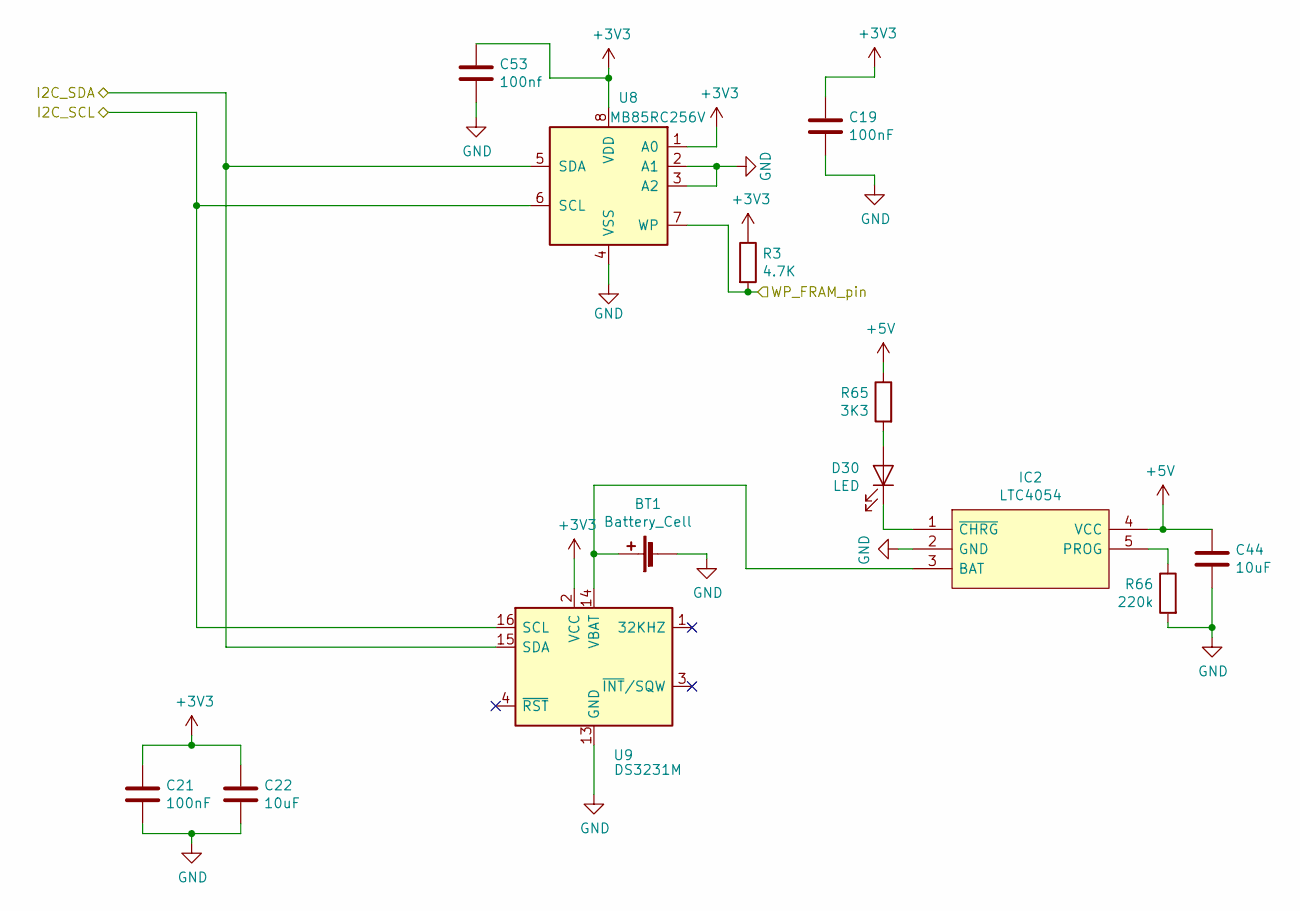
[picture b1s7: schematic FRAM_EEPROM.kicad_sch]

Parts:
BT1: Battery_Cell; BatteryHolder_Keystone_3034_1x20mm
C19, C21: 100nF; C_0603_1608Metric
C22, C44: 10uF; C_0603_1608Metric
C53: 100nf; C_0603_1608Metric
D30: LED; LED_0603_1608Metric
IC2: LTC4054; SOT-23-5; Manufacturer_Part_Number TP4054-42-SOT25-R
R3: 4.7K; R_0603_1608Metric
R65: 3K3; R_0603_1608Metric
R66: 220k; R_0603_1608Metric
U8: MB85RC256V; SOIC-8_3.9x4.9mm_P1.27mm
U9: DS3231M; SOIC-16W_7.5x10.3mm_P1.27mm

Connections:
+5V: C44.1, IC2.4 (VCC), R65.1; also elsewhere on the board
/ESP32/I2C_SCL: U8.6 (SCL), U9.16 (SCL); also elsewhere on the board
/ESP32/I2C_SDA: U8.5 (SDA), U9.15 (SDA); also elsewhere on the board
/ESP32/WP_FRAM_pin: R3.2, U8.7 (WP); also elsewhere on the board
GND: BT1.2 (-), C19.2, C21.2, C22.2, C44.2, C53.2, IC2.2 (GND), R66.2, U8.2 (A1), U8.3 (A2), U8.4 (VSS), U9.5 (GND), U9.6 (GND), U9.7 (GND), U9.8 (GND), U9.9 (GND), U9.10 (GND), U9.11 (GND), U9.12 (GND), U9.13 (GND); also elsewhere on the board
unnamed: BT1.1 (+), IC2.3 (BAT), U9.14 (VBAT)
unnamed: D30.1 (K), IC2.1 (~CHRG)
unnamed: D30.2 (A), R65.2
unnamed: IC2.5 (PROG), R66.1

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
